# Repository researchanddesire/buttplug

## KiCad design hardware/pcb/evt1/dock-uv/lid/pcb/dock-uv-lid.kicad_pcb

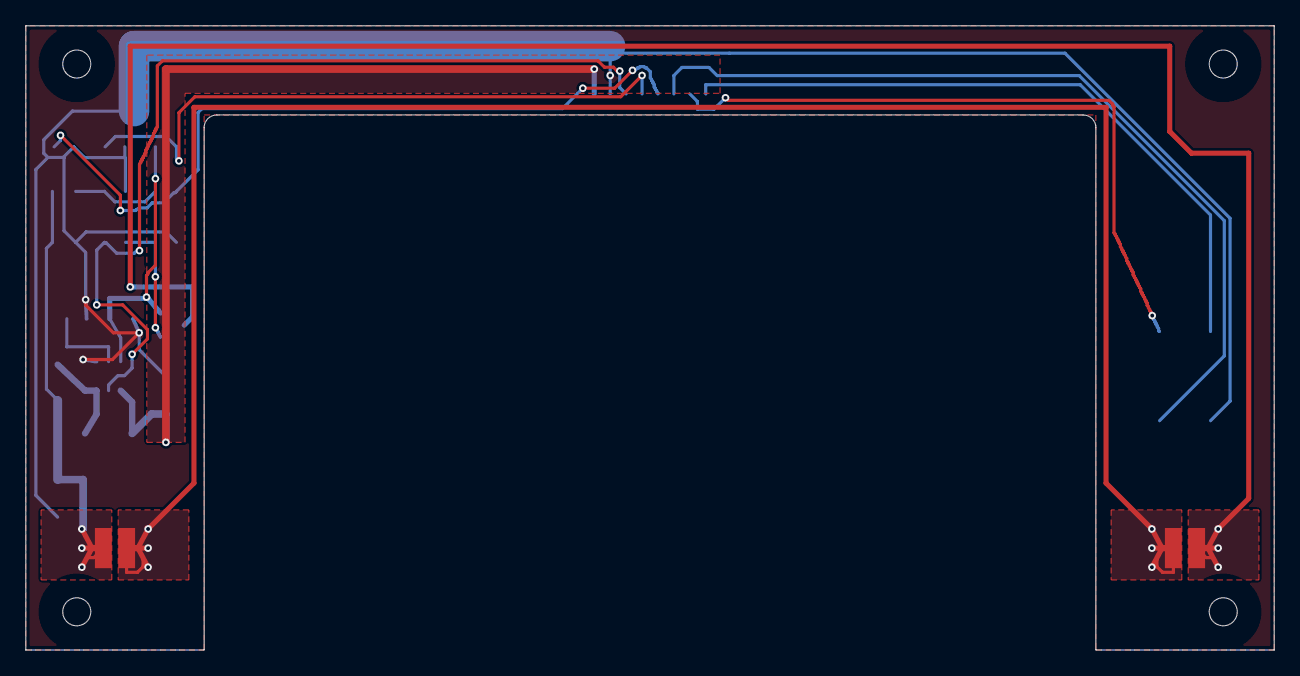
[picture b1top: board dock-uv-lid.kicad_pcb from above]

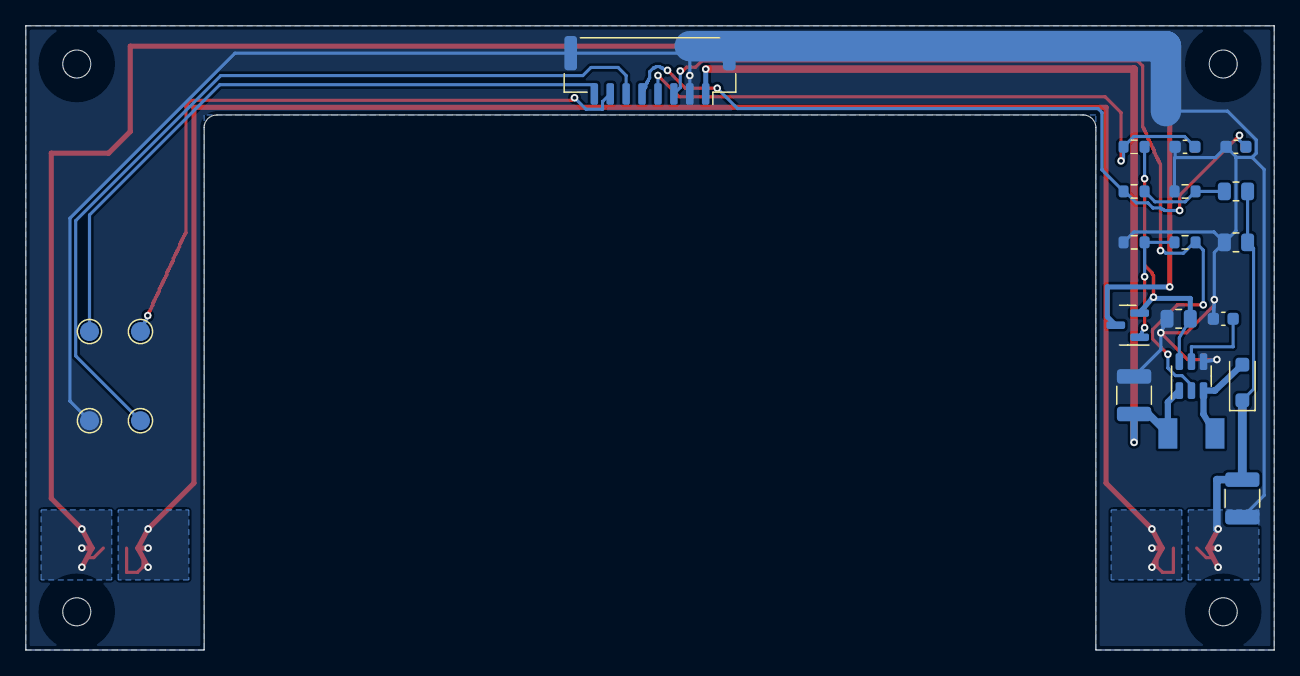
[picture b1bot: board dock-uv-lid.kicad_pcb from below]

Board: 2 copper layers, 98.0 x 49.0 mm, 28 parts (22 on the bottom side), 16 nets.

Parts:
C501, C502: 4.7uF50VX7R; C_1210_3225Metric
C503: 220nF25VX7R; C_0603_1608Metric
C504, C505: 100nF25VX7R; C_0603_1608Metric
D501: PMEG6010CEH,115; D_SOD-123F
D502, D503: VLMU35CB20-275-120; Vishay_VLMU35CB2_Actual_TwoTerminal
H501, H502, H503, H504: MountingHole_2.2mm_M2
J501: SM08B-GHS-TB; JST_GH_SM08B-GHS-TB_1x08-1MP_P1.25mm_Horizontal
L501: 10uH20% shielded; Bourns_SRP4020TA_Actual_Lands
Q501: DMN62D2U-7; SOT-23
R501: 3.65R1%100ppm; R_0805_2012Metric
R502: 1k1%; R_0603_1608Metric
R503: 100k1%; R_0603_1608Metric
R504: 100k1%; R_0805_2012Metric
R505: 1M1%; R_0805_2012Metric
R506: 68k1%; R_0603_1608Metric
R507, R508: 10k1%; R_0603_1608Metric
TP501: NTC_LID; TestPoint_Pad_D1.5mm
TP502: GND; TestPoint_Pad_D1.5mm
TP503: LID_THERM_SEND; TestPoint_Pad_D1.5mm
TP504: LOOP_B_RAW; TestPoint_Pad_D1.5mm
U501: TPS61165DBVR; SOT-23-6

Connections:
GND: C501.2, C502.2, C503.2, C504.2, C505.2, J501.2, J501.MP, R501.2, R503.2, R504.2, R506.2, TP502.1, U501.4
LID_CATHODE_GATE: Q501.1, R502.2, R503.1
LID_COMP: C503.1, U501.5
LID_FB: C504.1, J501.4, R508.2
LID_FB_RAW: Q501.2, R501.1, R508.1, U501.6
LID_LED_K: D503.1, Q501.3
LID_LED_MID: D502.1, D503.2
LID_SW: D501.2, L501.2, U501.3
LID_THERM_SEND: J501.7, TP503.1
LID_VOUT: C502.1, D501.1, D502.2, R504.1, R505.1
LID_VOUT_DIV: C505.1, J501.5, R507.2
LID_VOUT_SENSE: R505.2, R506.1, R507.1
LOOP_B_RAW: J501.8, TP504.1
NTC_LID: J501.6, TP501.1
UV_5V_SW: C501.1, J501.1, L501.1, U501.1
UV_CTRL: J501.3, R502.1, U501.2

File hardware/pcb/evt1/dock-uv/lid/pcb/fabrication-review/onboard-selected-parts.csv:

Reference,Manufacturer,MPN,Value,Footprint,PrimarySource,AssemblyNote
U501,Texas Instruments,TPS61165DBVR,TPS61165DBVR,DockUV:SOT-23-6,https://www.ti.com/lit/ds/symlink/tps61165.pdf,
L501,Bourns,SRP4020TA-100M,10uH20% shielded,DockUV:Bourns_SRP4020TA_Actual_Lands,https://www.bourns.com/docs/Product-Datasheets/SRP4020TA.pdf,
D501,Nexperia,"PMEG6010CEH,115","PMEG6010CEH,115",DockUV:D_SOD-123F,https://assets.nexperia.com/documents/data-sheet/PMEG6010CEH.pdf,"Exact orderable12NC934061056115,SOD123F_115,3000/reel: https://www.nexperia.com/product/PMEG6010CEH"
D502,Vishay,VLMU35CB20-275-120,VLMU35CB20-275-120,DockUV:Vishay_VLMU35CB2_Actual_TwoTerminal,https://www.vishay.com/docs/80232/vlmu35cb2x-275-120.pdf,Cathode mark must match pad1. Heatspreader/AlMCPCB must be qualified.
D503,Vishay,VLMU35CB20-275-120,VLMU35CB20-275-120,DockUV:Vishay_VLMU35CB2_Actual_TwoTerminal,https://www.vishay.com/docs/80232/vlmu35cb2x-275-120.pdf,
Q501,Diodes Incorporated,DMN62D2U-7,DMN62D2U-7,DockUV:SOT-23,https://www.diodes.com/datasheet/download/DMN62D2U.pdf,"Cathode disconnect separate from input cuts; source is FB, not GND."
J501,JST,SM08B-GHS-TB(LF)(SN),SM08B-GHS-TB,DockUV:JST_GH_SM08B-GHS-TB_1x08-1MP_P1.25mm_Horizontal,https://www.jst-mfg.com/product/pdf/eng/eGH.pdf,
R501,Vishay,CRCW08053R65FKEA,3.65R1%100ppm,DockUV:R_0805_2012Metric,https://www.vishay.com/docs/20035/dcrcwe3.pdf,
R502,Yageo,RC0603FR-071KL,1k1%,DockUV:R_0603_1608Metric,https://www.yageogroup.com/component-documentation/download/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,
R503,Yageo,RC0603FR-07100KL,100k1%,DockUV:R_0603_1608Metric,https://www.yageogroup.com/component-documentation/download/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,
R504,Yageo,RC0805FR-07100KL,100k1%,DockUV:R_0805_2012Metric,https://www.yageogroup.com/component-documentation/download/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,
R505,Yageo,RC0805FR-071ML,1M1%,DockUV:R_0805_2012Metric,https://www.yageogroup.com/component-documentation/download/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,
R506,Yageo,RC0603FR-0768KL,68k1%,DockUV:R_0603_1608Metric,https://www.yageogroup.com/component-documentation/download/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,
R507,Yageo,RC0603FR-0710KL,10k1%,DockUV:R_0603_1608Metric,https://www.yageogroup.com/component-documentation/download/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,
R508,Yageo,RC0603FR-0710KL,10k1%,DockUV:R_0603_1608Metric,https://www.yageogroup.com/component-documentation/download/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,
C501,TDK,C3225X7R1H475K250AB,4.7uF50VX7R,DockUV:C_1210_3225Metric,https://product.tdk.com/en/search/capacitor/ceramic/mlcc/inf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,"Require >=1uF effective over VIN4.3..5.25V/input or VOUT0..39V/output,temp,age. TI output recommendation1..10uF."
C502,TDK,C3225X7R1H475K250AB,4.7uF50VX7R,DockUV:C_1210_3225Metric,https://product.tdk.com/en/search/capacitor/ceramic/mlcc/inf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,"Require >=1uF effective over VIN4.3..5.25V/input or VOUT0..39V/output,temp,age. TI output recommendation1..10uF."
C503,TDK,C1608X7R1E224K080AC,220nF25VX7R,DockUV:C_0603_1608Metric,https://product.tdk.com/en/search/capacitor/ceramic/mlcc/inf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,
C504,TDK,C1608X7R1E104K080AA,100nF25VX7R,DockUV:C_0603_1608Metric,https://product.tdk.com/en/search/capacitor/ceramic/mlcc/inf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,
C505,TDK,C1608X7R1E104K080AA,100nF25VX7R,DockUV:C_0603_1608Metric,https://product.tdk.com/en/search/capacitor/ceramic/mlcc/inf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,

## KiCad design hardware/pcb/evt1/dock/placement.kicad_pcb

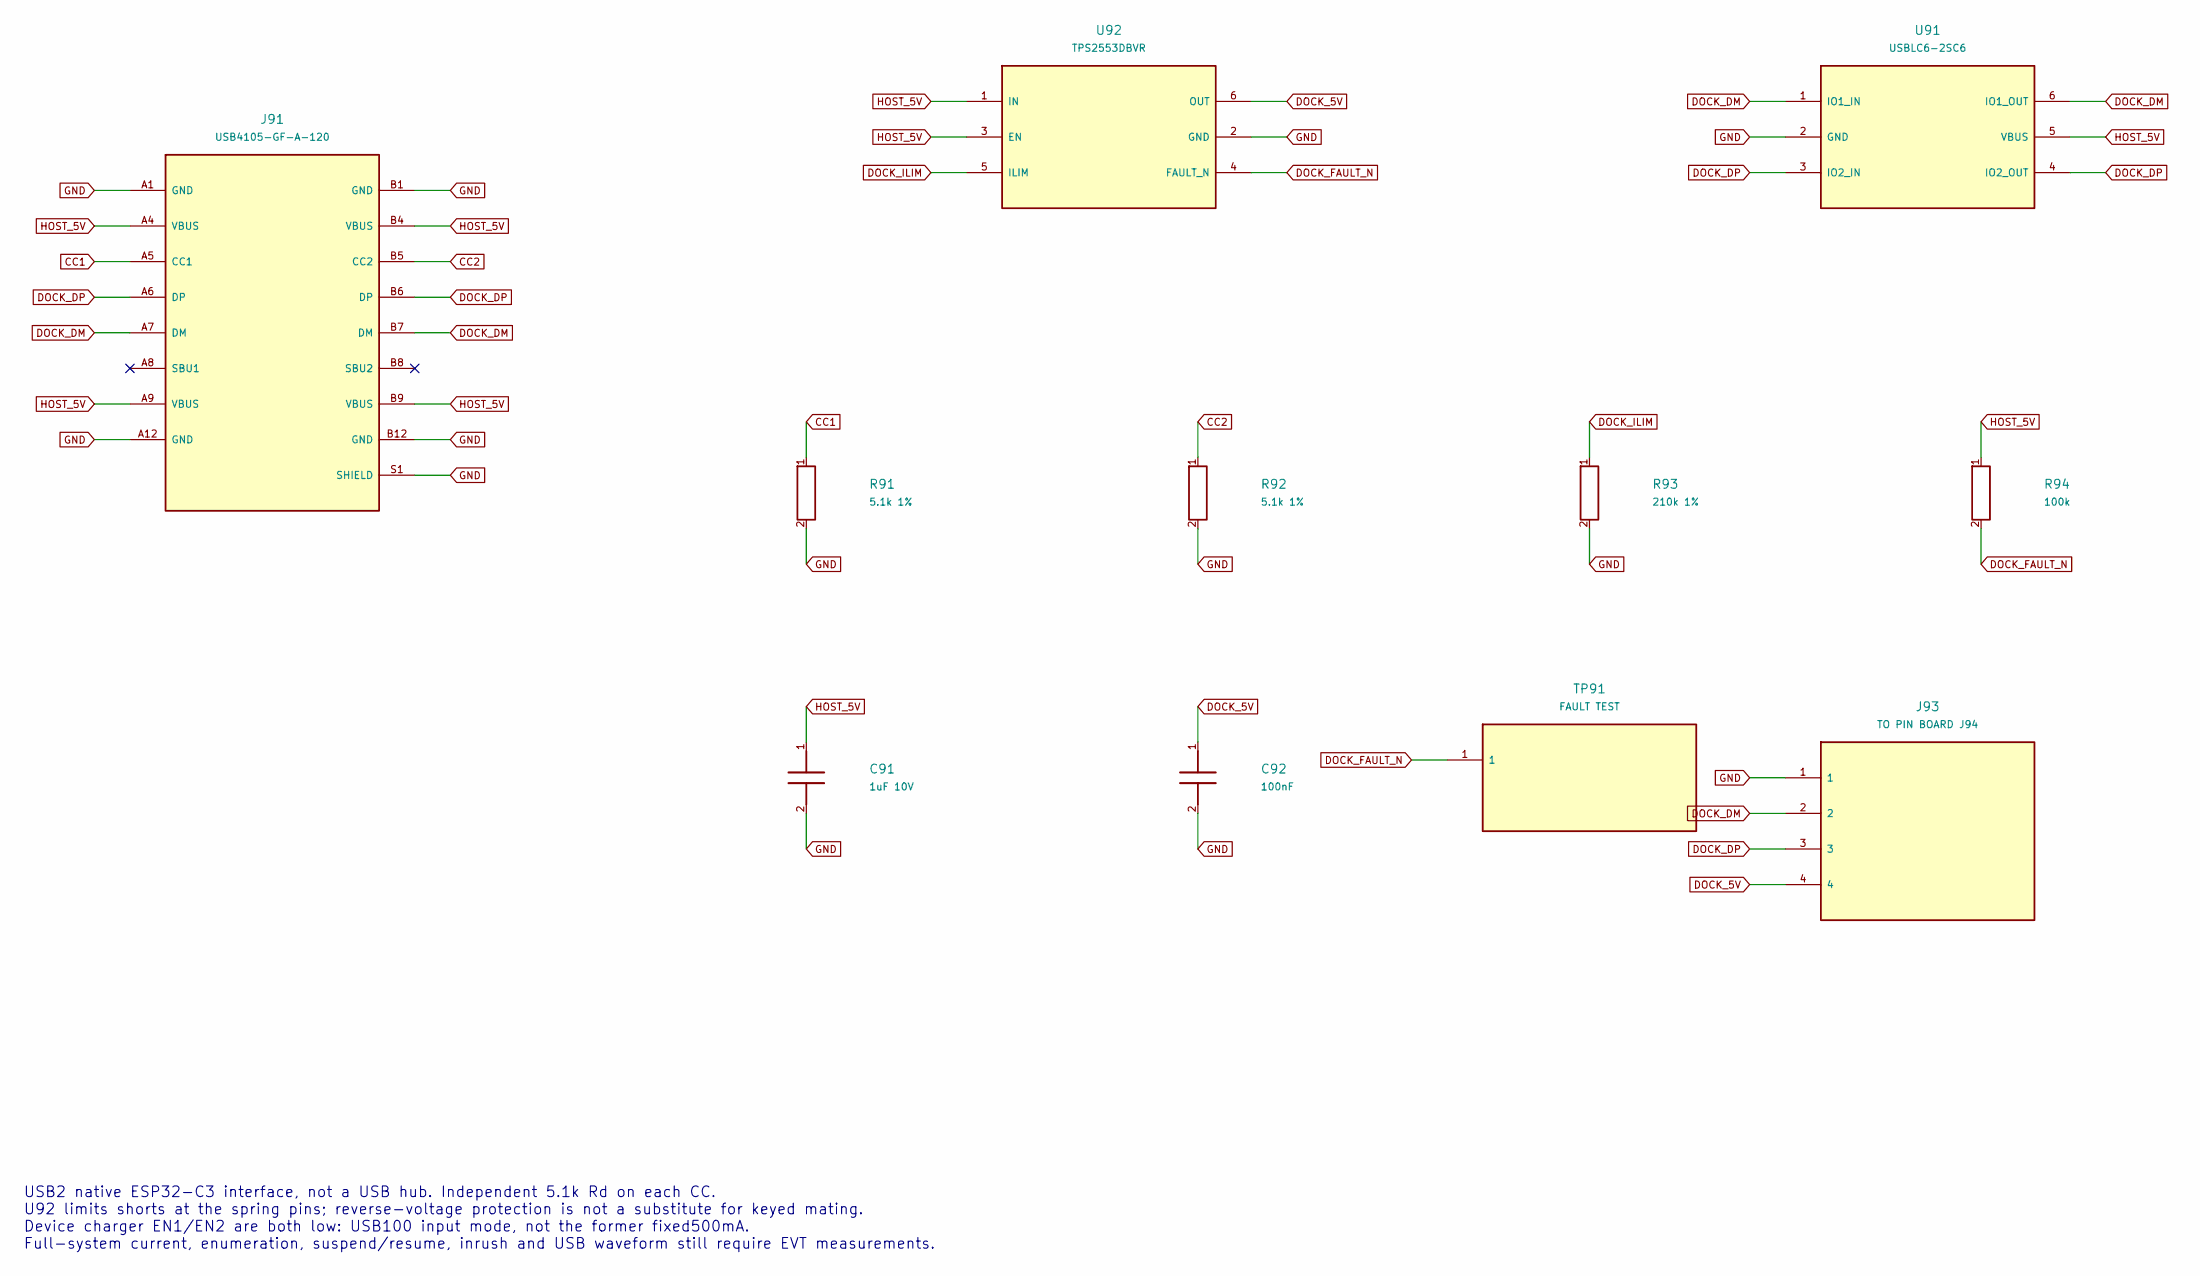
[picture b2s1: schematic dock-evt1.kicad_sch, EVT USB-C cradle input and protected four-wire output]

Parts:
C91: 1uF 10V; C_0603_1608Metric
C92: 100nF; C_0402_1005Metric
J91: USB4105-GF-A-120; USB_C_Receptacle_GCT_USB4105-xx-A_16P_TopMnt_Horizontal
J93: TO PIN BOARD J94; Contact_Loom_4Land
R91, R92: 5.1k 1%; R_0402_1005Metric
R93: 210k 1%; R_0402_1005Metric
R94: 100k; R_0402_1005Metric
TP91: FAULT TEST; TestPoint_Pad_D1.0mm
U91: USBLC6-2SC6; SOT-23-6
U92: TPS2553DBVR; SOT-23-6

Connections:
CC1: J91.A5 (CC1), R91.1
CC2: J91.B5 (CC2), R92.1
DOCK_5V: C92.1, J93.4, U92.6 (OUT)
DOCK_DM: J91.A7 (DM), J91.B7 (DM), J93.2, U91.1 (IO1_IN), U91.6 (IO1_OUT)
DOCK_DP: J91.A6 (DP), J91.B6 (DP), J93.3, U91.3 (IO2_IN), U91.4 (IO2_OUT)
DOCK_FAULT_N: R94.2, TP91.1, U92.4 (FAULT_N)
DOCK_ILIM: R93.1, U92.5 (ILIM)
GND: C91.2, C92.2, J91.A1 (GND), J91.A12 (GND), J91.B1 (GND), J91.B12 (GND), J91.S1 (SHIELD), J93.1, R91.2, R92.2, R93.2, U91.2 (GND), U92.2 (GND)
HOST_5V: C91.1, J91.A4 (VBUS), J91.A9 (VBUS), J91.B4 (VBUS), J91.B9 (VBUS), R94.1, U91.5 (VBUS), U92.1 (IN), U92.3 (EN)

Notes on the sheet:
USB2 native ESP32-C3 interface, not a USB hub. Independent 5.1k Rd on each CC. U92 limits shorts at the spring pins; reverse-voltage protection is not a substitute for keyed mating. Device charger EN1/EN2 are both low: USB100 input mode, not the former fixed500mA. Full-system current, enumeration, 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

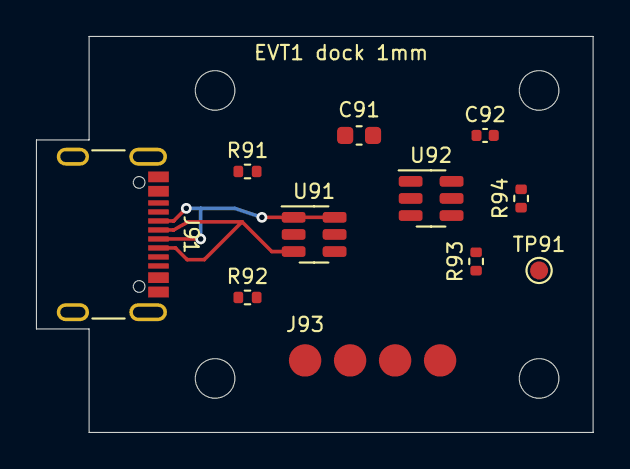
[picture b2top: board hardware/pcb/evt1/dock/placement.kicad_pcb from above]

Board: 2 copper layers, 30.9 x 22.0 mm, 15 parts (0 on the bottom side), 9 nets.

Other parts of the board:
H1, H2, H3, H4: MountingHole_2.2mm_M2

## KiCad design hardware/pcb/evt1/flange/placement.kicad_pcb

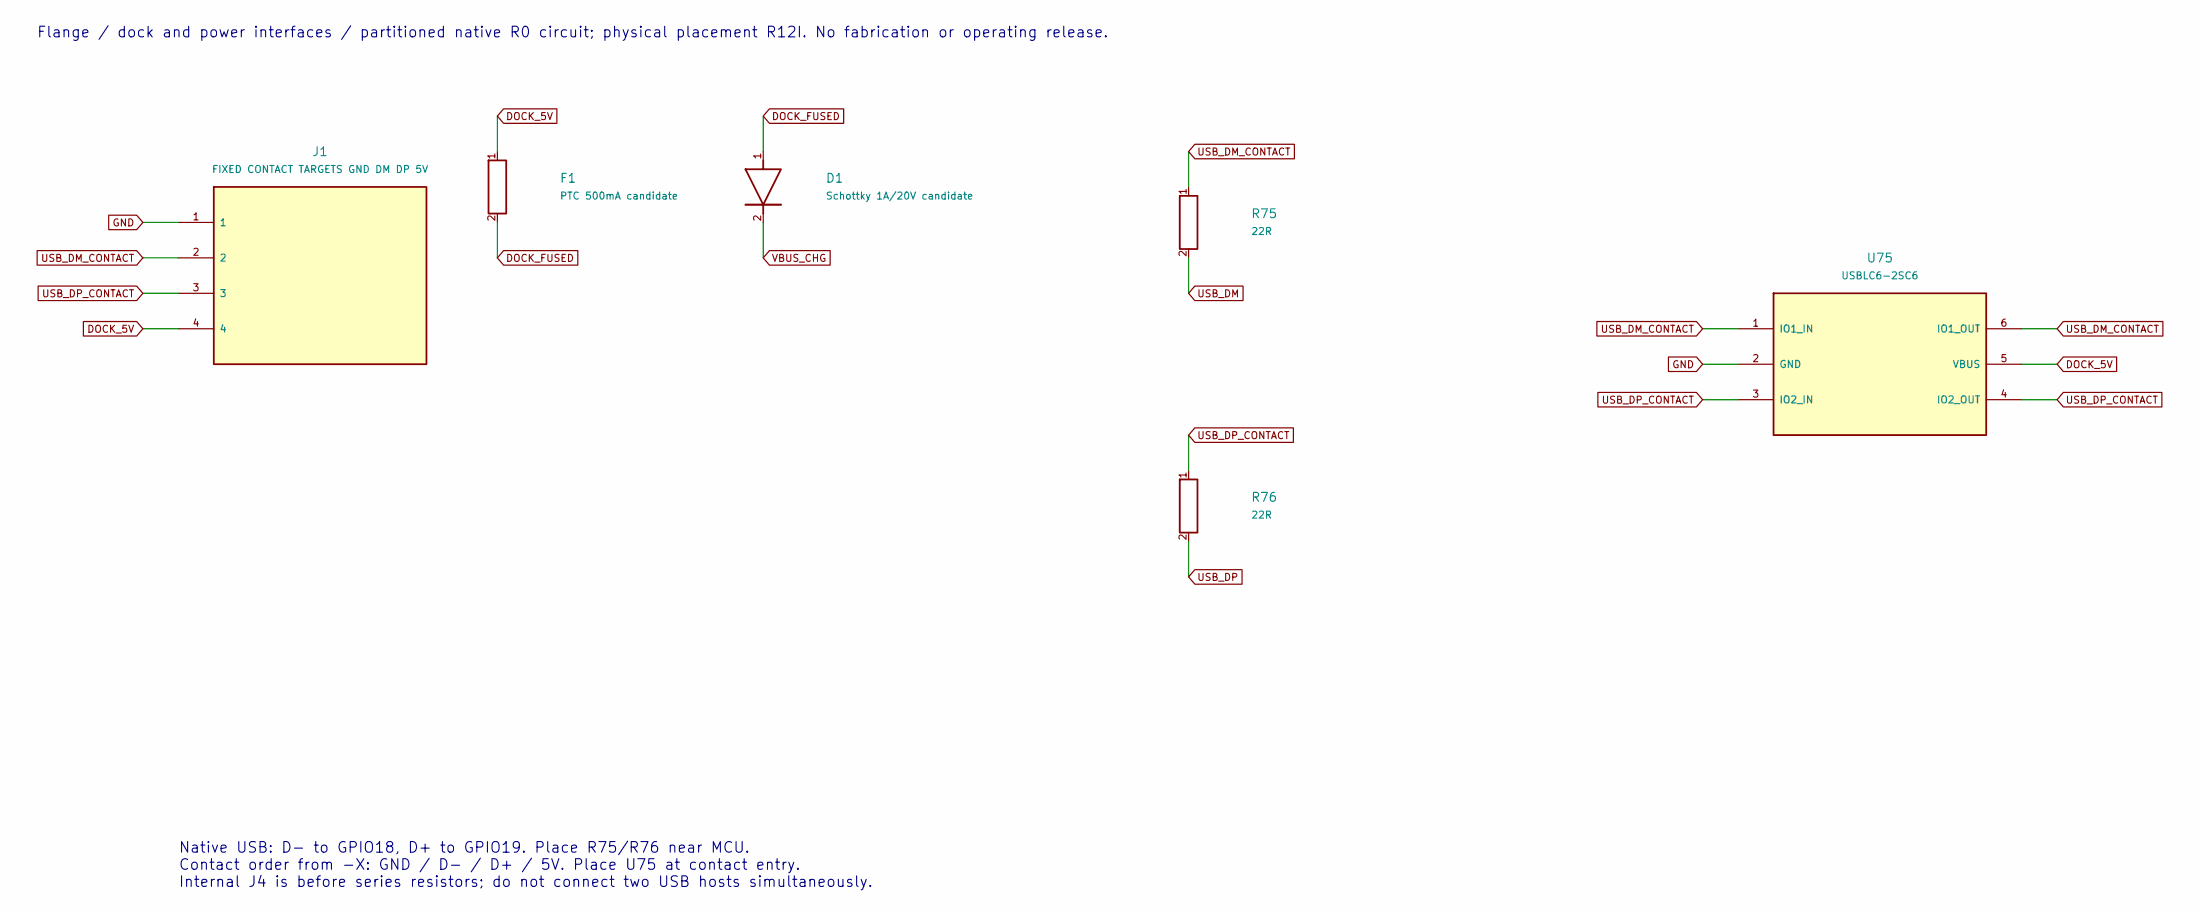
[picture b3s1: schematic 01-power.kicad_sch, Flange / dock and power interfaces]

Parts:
D1: Schottky 1A/20V candidate; Diodes_B140HW_SOD123_A1_K2
F1: PTC 500mA candidate; Fuse_1206_3216Metric
J1: FIXED CONTACT TARGETS GND DM DP 5V; Contact_Loom_4Land
R75, R76: 22R; R_0402_1005Metric
U75: USBLC6-2SC6; SOT-23-6

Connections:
DOCK_5V: F1.1, J1.4, U75.5 (VBUS)
DOCK_FUSED: D1.1, F1.2
GND: J1.1, U75.2 (GND); also elsewhere on the board
USB_DM: R75.2; also elsewhere on the board
USB_DM_CONTACT: J1.2, R75.1, U75.1 (IO1_IN), U75.6 (IO1_OUT)
USB_DP: R76.2; also elsewhere on the board
USB_DP_CONTACT: J1.3, R76.1, U75.3 (IO2_IN), U75.4 (IO2_OUT)
VBUS_CHG: D1.2; also elsewhere on the board

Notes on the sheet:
Flange / dock and power interfaces / partitioned native R0 circuit; physical placement R12I. No fabrication or operating release.
Native USB: D- to GPIO18, D+ to GPIO19. Place R75/R76 near MCU. Contact order from -X: GND / D- / D+ / 5V. Place U75 at contact entry. Internal J4 is before series resistors; do not connect two USB hosts simultaneously.

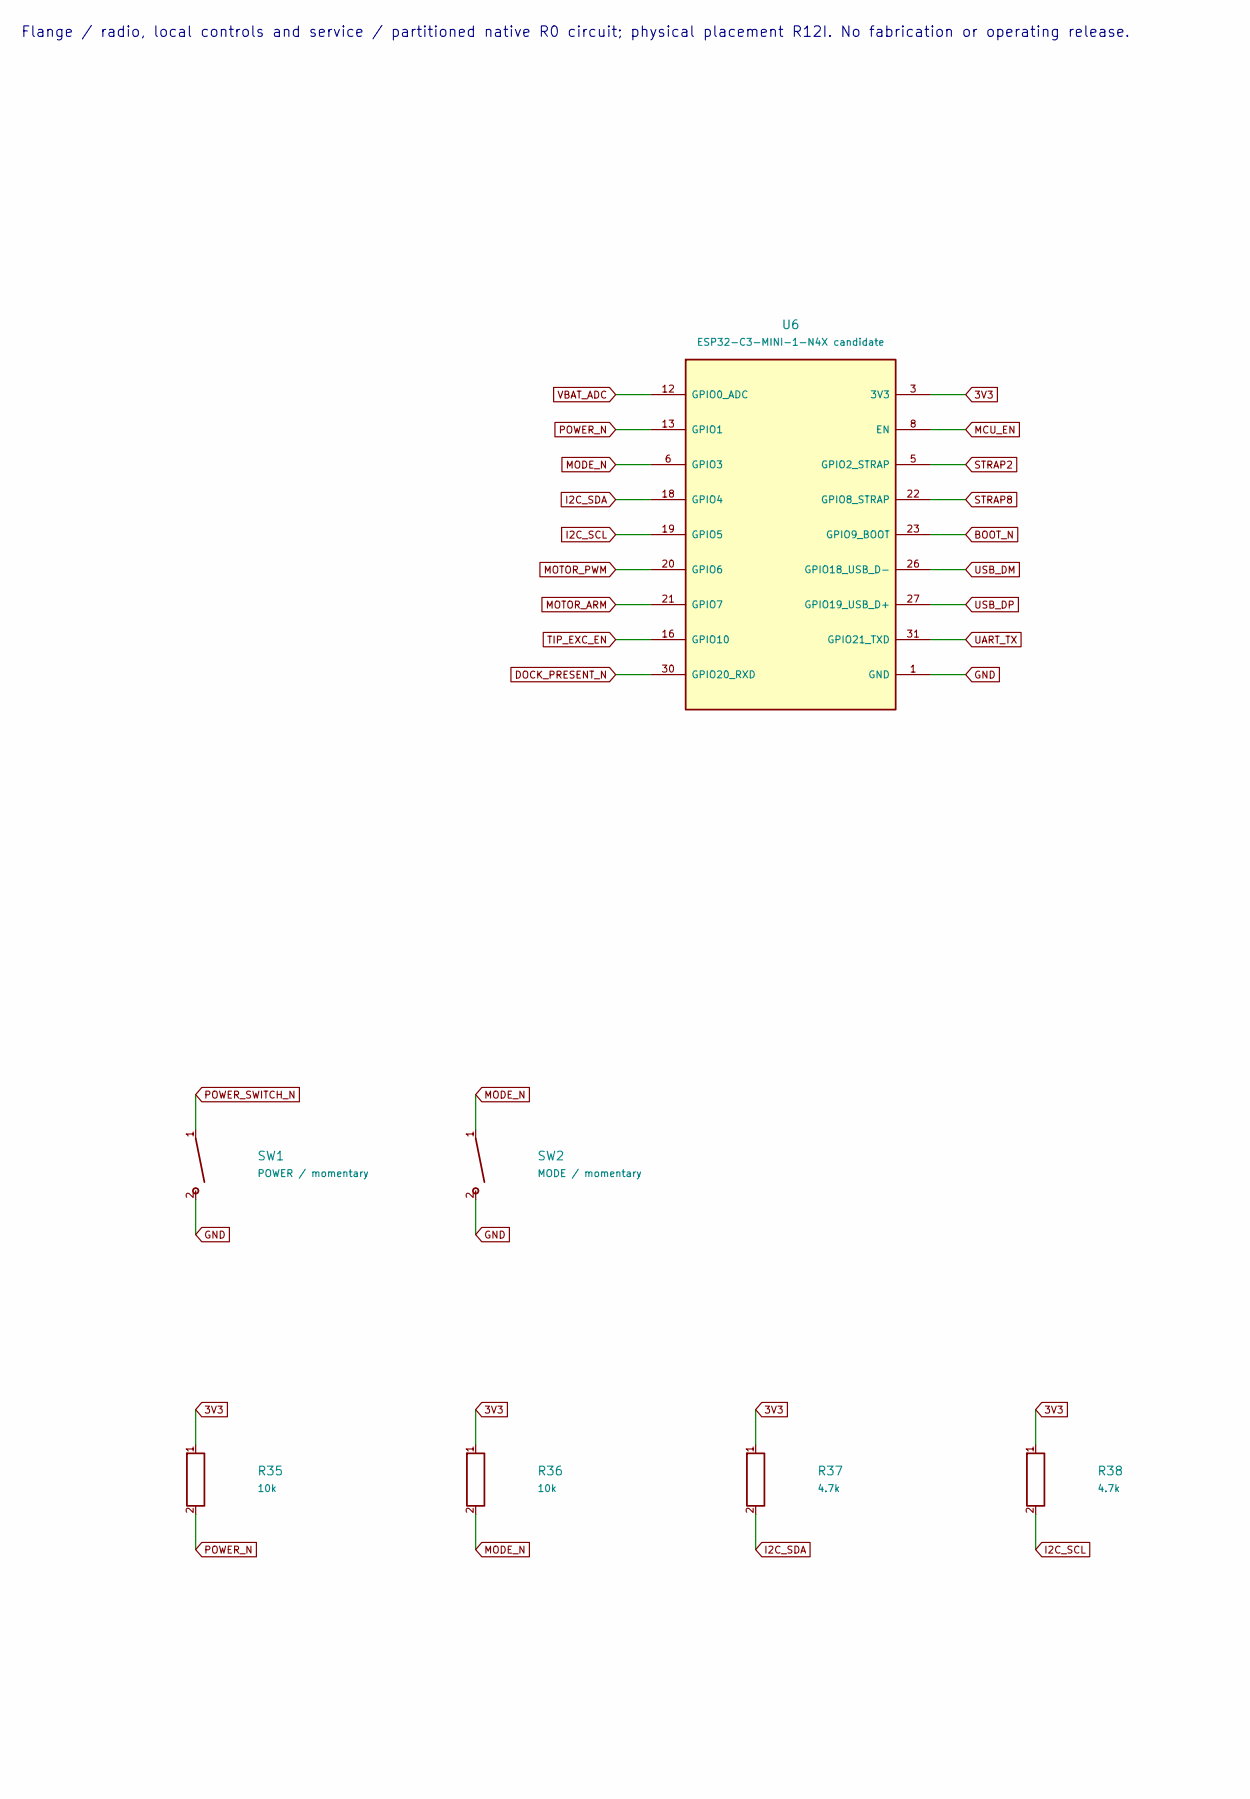
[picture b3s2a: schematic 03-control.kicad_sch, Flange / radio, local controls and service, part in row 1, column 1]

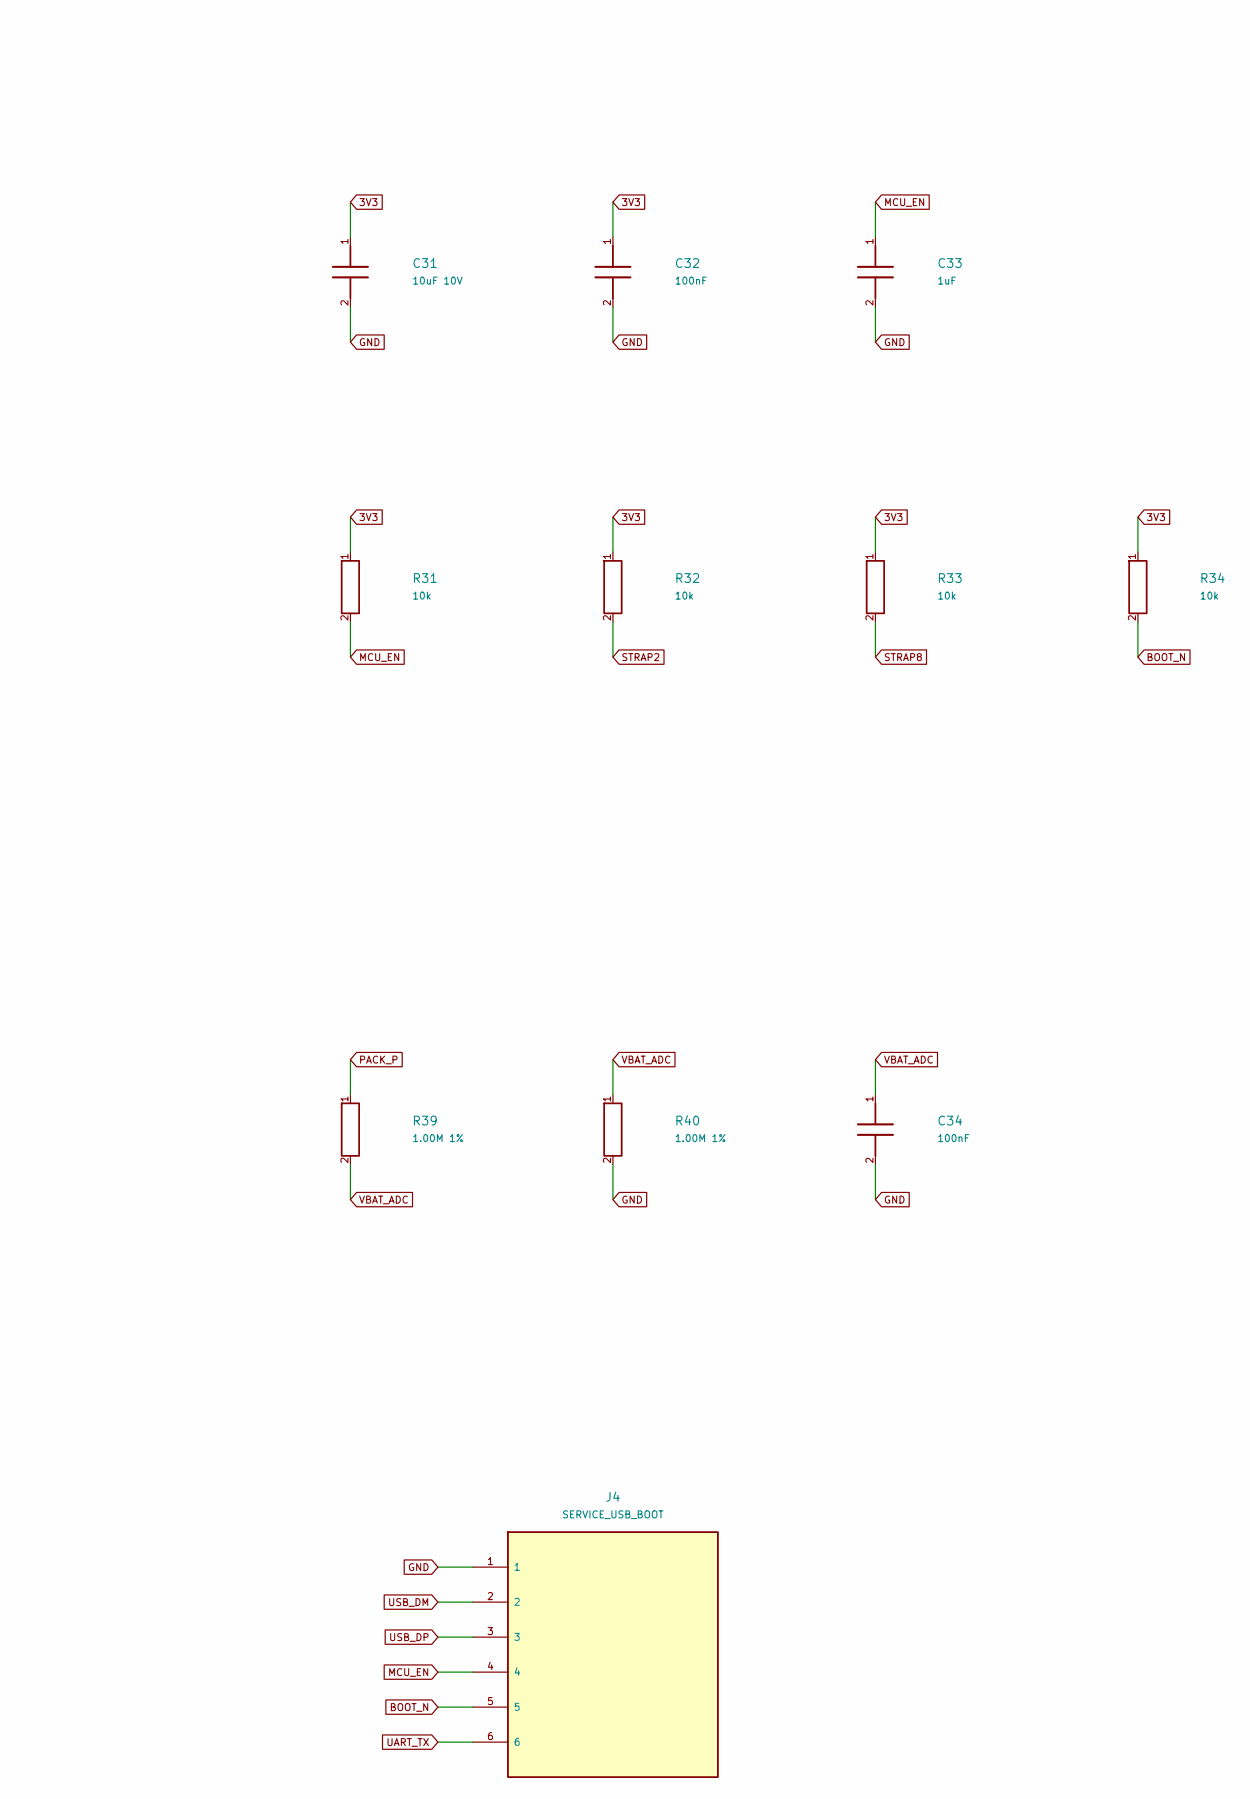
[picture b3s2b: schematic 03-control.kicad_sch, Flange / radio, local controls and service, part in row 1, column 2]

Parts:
C31: 10uF 10V; Murata_GRM21_0805_Reflow
C32, C34: 100nF; Murata_GRM18_0603_Reflow
C33: 1uF; TDK_C1608_0603_Reflow
J4: SERVICE_USB_BOOT; JST_SH_SM06B-SRSS-TB_1x06-1MP_P1.00mm_Horizontal
R31, R32, R33, R34, R35, R36: 10k; Vishay_TNPW0603_IEC_Reflow
R37, R38: 4.7k; Vishay_TNPW0603_IEC_Reflow
R39, R40: 1.00M 1%; Vishay_TNPW0805_IEC_Reflow
SW1: POWER / momentary; SW_SPST_B3U-1000P
SW2: MODE / momentary; SW_SPST_B3U-1000P
U6: ESP32-C3-MINI-1-N4X candidate; Espressif_ESP32-C3-MINI-1_53Pads

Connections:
3V3: C31.1, C32.1, R31.1, R32.1, R33.1, R34.1, R35.1, R36.1, R37.1, R38.1, U6.3 (3V3); also elsewhere on the board
BOOT_N: J4.5, R34.2, U6.23 (GPIO9_BOOT); also elsewhere on the board
DOCK_PRESENT_N: U6.30 (GPIO20_RXD); also elsewhere on the board
GND: C31.2, C32.2, C33.2, C34.2, J4.1, R40.2, SW1.2, SW2.2, U6.1 (GND), U6.2 (GND), U6.11 (GND), U6.14 (GND), U6.36 (GND), U6.37 (GND), U6.38 (GND), U6.39 (GND), U6.40 (GND), U6.41 (GND), U6.42 (GND), U6.43 (GND), U6.44 (GND), U6.45 (GND), U6.46 (GND), U6.47 (GND), U6.48 (GND), U6.49 (GND), U6.50 (GND), U6.51 (GND), U6.52 (GND), U6.53 (GND); also elsewhere on the board
I2C_SCL: R38.2, U6.19 (GPIO5); also elsewhere on the board
I2C_SDA: R37.2, U6.18 (GPIO4); also elsewhere on the board
MCU_EN: C33.1, J4.4, R31.2, U6.8 (EN); also elsewhere on the board
MODE_N: R36.2, SW2.1, U6.6 (GPIO3); also elsewhere on the board
MOTOR_ARM: U6.21 (GPIO7); also elsewhere on the board
MOTOR_PWM: U6.20 (GPIO6); also elsewhere on the board
PACK_P: R39.1; also elsewhere on the board
POWER_N: R35.2, U6.13 (GPIO1); also elsewhere on the board
POWER_SWITCH_N: SW1.1; also elsewhere on the board
STRAP2: R32.2, U6.5 (GPIO2_STRAP)
STRAP8: R33.2, U6.22 (GPIO8_STRAP)
TIP_EXC_EN: U6.16 (GPIO10); also elsewhere on the board
UART_TX: J4.6, U6.31 (GPIO21_TXD)
USB_DM: J4.2, U6.26 (GPIO18_USB_D-); also elsewhere on the board
USB_DP: J4.3, U6.27 (GPIO19_USB_D+); also elsewhere on the board
VBAT_ADC: C34.1, R39.2, R40.1, U6.12 (GPIO0_ADC)

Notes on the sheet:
Flange / radio, local controls and service / partitioned native R0 circuit; physical placement R12I. No fabrication or operating release.

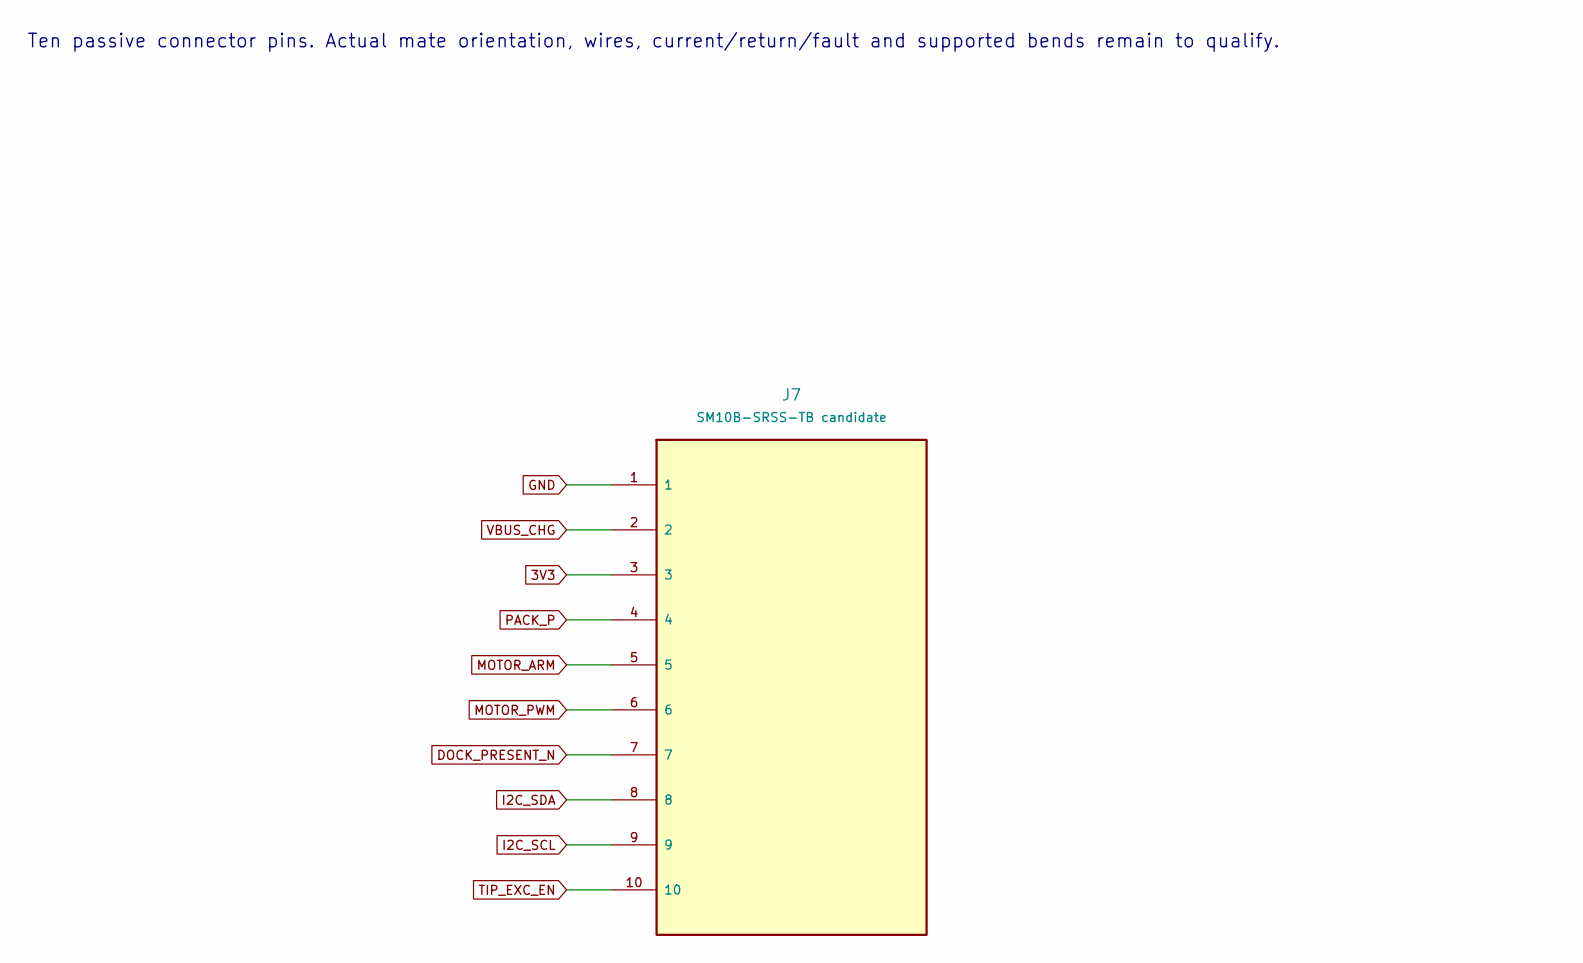
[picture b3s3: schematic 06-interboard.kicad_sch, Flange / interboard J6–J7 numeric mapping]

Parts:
J7: SM10B-SRSS-TB candidate; JST_SH_SM10B-SRSS-TB_1x10-1MP_P1.00mm_Horizontal

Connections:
3V3: J7.3; also elsewhere on the board
DOCK_PRESENT_N: J7.7; also elsewhere on the board
GND: J7.1; also elsewhere on the board
I2C_SCL: J7.9; also elsewhere on the board
I2C_SDA: J7.8; also elsewhere on the board
MOTOR_ARM: J7.5; also elsewhere on the board
MOTOR_PWM: J7.6; also elsewhere on the board
PACK_P: J7.4; also elsewhere on the board
TIP_EXC_EN: J7.10; also elsewhere on the board
VBUS_CHG: J7.2; also elsewhere on the board

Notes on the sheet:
Ten passive connector pins. Actual mate orientation, wires, current/return/fault and supported bends remain to qualify.

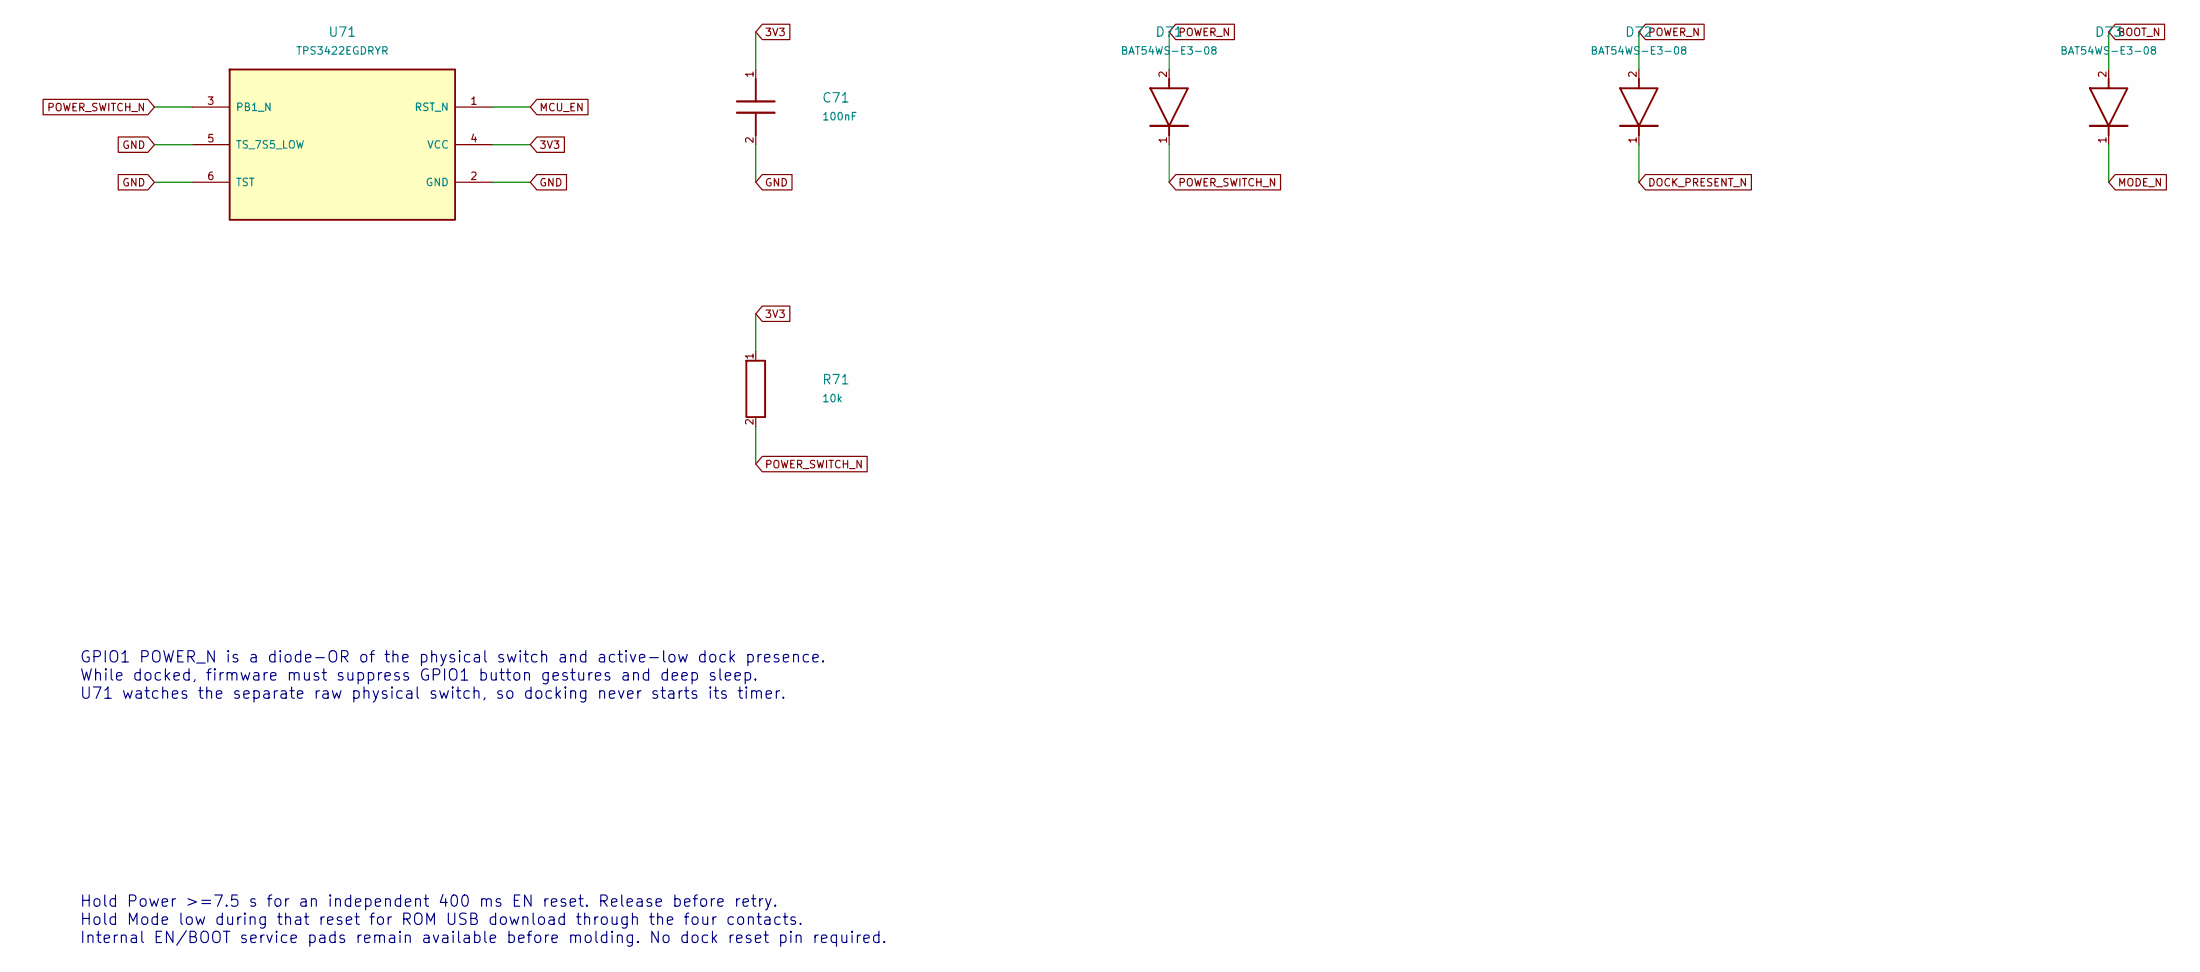
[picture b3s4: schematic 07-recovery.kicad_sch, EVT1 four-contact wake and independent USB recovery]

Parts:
C71: 100nF; C_0402_1005Metric
D71, D72, D73: BAT54WS-E3-08; D_SOD-323
R71: 10k; R_0402_1005Metric
U71: TPS3422EGDRYR; Texas_USON-6_1x1.45mm_P0.5mm_SMD

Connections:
3V3: C71.1, R71.1, U71.4 (VCC); also elsewhere on the board
BOOT_N: D73.2 (1); also elsewhere on the board
DOCK_PRESENT_N: D72.1 (2); also elsewhere on the board
GND: C71.2, U71.2 (GND), U71.5 (TS_7S5_LOW), U71.6 (TST); also elsewhere on the board
MCU_EN: U71.1 (RST_N); also elsewhere on the board
MODE_N: D73.1 (2); also elsewhere on the board
POWER_N: D71.2 (1), D72.2 (1); also elsewhere on the board
POWER_SWITCH_N: D71.1 (2), R71.2, U71.3 (PB1_N); also elsewhere on the board

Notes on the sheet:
GPIO1 POWER_N is a diode-OR of the physical switch and active-low dock presence. While docked, firmware must suppress GPIO1 button gestures and deep sleep. U71 watches the separate raw physical switch, so docking never starts its timer.
Hold Power >=7.5 s for an independent 400 ms EN reset. Release before retry. Hold Mode low during that reset for ROM USB download through the four contacts. Internal EN/BOOT service pads remain available before molding. No dock reset pin required.
